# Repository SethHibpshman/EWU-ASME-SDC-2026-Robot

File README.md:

# EWU ASME SDC 2026 Robot

> A remotely controlled garbage truck robot built for the 2026 ASME Student Design Competition, featuring a custom KiCad PCB and power distribution board, Arduino iBUS teleoperation, rear wheel drive with servo steering, a robotic arm, and a rotary dumping bucket. **3rd place overall.**

> The original written papers (the full ASME SDC report and the battery analysis) are in [`/docs`](/docs). The KiCad PCB files and 3D models are in [`/hardware`](/hardware).

## Table of Contents

- [Overview](#overview)
- [Functionality](#functionality)
  - [Operating Requirements](#operating-requirements)
  - [Drive and Steering](#drive-and-steering)
  - [Manipulation and Dumping](#manipulation-and-dumping)
  - [Radio Control Mapping](#radio-control-mapping)
  - [Input Processing and Failsafe](#input-processing-and-failsafe)
- [System Design](#system-design)
  - [Hardware](#hardware)
  - [Power Architecture](#power-architecture)
  - [Battery Selection Analysis](#battery-selection-analysis)
  - [PCB Design](#pcb-design)
  - [Power Distribution Board](#power-distribution-board)
  - [Software](#software)
  - [Mechanical Design](#mechanical-design)
- [Design Tradeoffs](#design-tradeoffs)
- [Competition Results](#competition-results)
- [Lessons Learned and Future Improvements](#lessons-learned-and-future-improvements)
- [Bill of Materials](#bill-of-materials)
- [Team](#team)
- [AI Disclosure](#ai-disclosure)
- [License](#license)

## Overview

The 2026 ASME SDC challenges teams to design, fabricate, and test a versatile waste collection device that can navigate a model "downtown Dallas", collect and sort garbage and recycling, and dump it into the correct facility (landfill or recycling center) without damaging the playfield or spilling waste.

This robot is a compact, fully teleoperated garbage truck built by the Eastern Washington University ASME chapter. It combines a custom electrical system, Arduino based control logic, a FlySky radio link, a 3D printed PETG chassis, and a servo driven arm that feeds a rotary dumping bucket. It reached the final head-to-head matchup against the top-seeded team and finished **third overall**.

The electrical and control work also served as applied coursework for **EENG 163: Introduction to Embedded Systems** at Eastern Washington University.

## Functionality

### Operating Requirements

The robot had to satisfy the following competition rules:

| Category | Requirement |
|---|---|
| **Size** | Fit inside a 50 cm x 50 cm x 50 cm box, including batteries and tools |
| **Power** | Rechargeable dry cell batteries only, with onboard distribution and no tethering |
| **Control** | Single operator, single radio transmitter |
| **Runs** | 5 to 10 minute timed runs, timer never paused |
| **Repairs** | Battery swaps and wire reconnection allowed on the clock, no soldering or reprogramming |
| **Safety** | No playfield damage, no interference with other robots, unsafe behavior means disqualification |
| **Course** | Navigate 10 to 18 cm wide streets with 90 and 180 degree turns |

### Drive and Steering

| Feature | Behavior |
|---|---|
| **Rear drive** | Two geared yellow DC motors with rubber wheels, driven by a brushed DC H-bridge with forward and reverse PWM |
| **Front steering** | Servo steering through 3D printed control arms, clamped to a safe pulse range |
| **Deadband** | Neutral zone around center throttle prevents unintended motion and drift |
| **Throttle smoothing** | Exponential smoothing reduces jitter and drivetrain current spikes |

### Manipulation and Dumping

| Feature | Behavior |
|---|---|
| **Arm** | Servo driven arm with gripper and shoulder joint, designed by David Alvarado |
| **Shoulder motion** | Stepped slowly toward its target angle for smooth, controlled movement |
| **Arm to dumper slide** | At a 35 degree arm angle, nearly any material slides from the small receptacle into the dumper |
| **Rotary dumper** | Servo tips the bucket with analog control so contents slide out smoothly into the large receptacle |

### Radio Control Mapping

| Channel | Function | Pin |
|---|---|---|
| CH1 | Steering servo | D2 |
| CH2 | Drive motor throttle (FWD / REV) | D9 / D10 |
| CH3 | Auxiliary servo | D4 |
| CH5 | Gripper servo | D3 |
| CH6 | Shoulder servo | D5 |

> Mapping is taken from the firmware v10.0.0 listing. Confirm against your sketch before publishing.

### Input Processing and Failsafe

- **iBUS decoding:** frames from the FlySky FS-iA6B are read on hardware serial and parsed in software
- **Checksum validation:** corrupted frames are discarded
- **Normalization:** channel values map to roughly 1000 to 2000 µs pulse widths, then to actuator specific ranges
- **Failsafe:** the receiver returns outputs to neutral on signal loss, which stops the motors

## System Design

### Hardware

| Component | Details |
|---|---|
| Microcontroller | Arduino Nano Every |
| Radio | FlySky FS-iA6B receiver (iBUS serial) with FlySky transmitter |
| Battery | 6x NiMH AA in series, 7.2 V nominal |
| Regulation | LM2596 buck converter module, 5 V logic rail |
| Motor driver | Brushed DC H-bridge |
| Drive motors | 2x geared yellow DC motors |
| Servos | SG90 and MG995 types (see BOM) |
| Capacitance | 4x 1000 µF electrolytic (4000 µF bulk) |
| Structure | 3D printed PETG |

### Power Architecture

The design separates power into two domains so motor noise cannot reset the microcontroller.

```mermaid
flowchart LR
    BAT["6x NiMH AA pack<br/>7.2 V nominal"] --> SW["Power switch"]
    SW --> PDB["Power Distribution Board<br/>4000 uF bulk capacitance"]

    PDB -- "raw battery rail" --> HB["Brushed DC H-bridge"]
    PDB -- "raw battery rail" --> HTS["High torque servos"]
    PDB -- "soldered harness" --> BUCK["LM2596 buck converter<br/>on control PCB"]

    BUCK -- "5 V" --> MCU["Arduino Nano Every"]
    BUCK -- "5 V" --> RX["FS-iA6B receiver"]
    BUCK -- "5 V" --> LTS["Low torque servos"]

    MCU -- "PWM" --> HB
    MCU -- "servo PWM" --> HTS
    MCU -- "servo PWM" --> LTS
    HB --> MOT["2x DC drive motors"]
```

- Unregulated battery voltage feeds the motor driver and high torque servos directly, avoiding current limits and voltage drops from a regulator
- 4000 µF of bulk capacitance absorbs transients from motor acceleration and steering
- Regulation is reserved for logic level components only

### Battery Selection Analysis

Pack selection came from an EENG 163 research project (February 2026). Each pack is modeled as an ideal source with internal resistance:

$$V_{load} = V_{nominal} - I_{draw} \cdot R_{internal}$$

Targets were a **2 A** worst case load and a **6 V** minimum so the buck converter could hold a stable 5 V.

| Parameter | Alkaline 9 V | Alkaline AA | NiMH AA |
|---|---|---|---|
| Nominal voltage per cell | 9 V | 1.5 V | 1.2 V |
| Internal resistance per cell | 1.5 Ω | 0.15 Ω | 0.02 Ω |
| Max continuous current | 0.1 A | 1 A | 3 A |
| Tested pack | 1 cell | 6 in series | 6 in series |
| Pack voltage / resistance | 9 V / 1.5 Ω | 9.0 V / 0.9 Ω | 7.2 V / 0.12 Ω |
| Voltage at 2 A | 6 V | 7.2 V | 6.96 V |
| Verdict | Unsafe, 20x over rating | Over 1 A rating | Safe, most robust |

$$\text{NiMH AA (6S): } V_{load} = 7.2 - 2(0.12) = 6.96\ \text{V}$$

> The analysis assumed a brushless motor. The final robot used low draw yellow DC motors instead, so the NiMH pack ran with extra margin.

### PCB Design

Designed in KiCad and fabricated through JLCPCB. All project files are in [`/hardware/KiCAD PCB`](</hardware/KiCAD PCB>).

- LM2596 buck converter footprint for the 5 V rail
- Arduino Nano Every mounted directly on the board
- Five male pin header interfaces plus separated ground and power rails in a 5x3 layout, usable with Dupont connectors or direct soldering
- Continuous ground plane to reduce noise coupling between motor circuits and logic

### Power Distribution Board

- Four 1000 µF capacitors across the main rail
- Integrated brushed DC H-bridge for the drive motors
- Physical power switch for fast shutdown during setup and repairs
- Three 3 pin headers supplying raw battery voltage to high torque servos, with control signals routed separately from the control PCB
- Joined to the control PCB by two soldered wire harnesses for vibration resistance

### Software

Arduino sketch (version 10.0.0) running on the Nano Every, adapted from SwapnilNimbalkar's iBUS to PWM receiver tutorial. The full listing is also in the appendix of the report in [`/docs`](/docs).

**Dependencies:** `Servo`

```
firmware/    # Arduino iBUS teleoperation sketch (.ino)
```

### Mechanical Design

*Written by Zachary Jump, with arm and dumper integration by David Alvarado. CAD files are in [`/hardware/3D Models`](</hardware/3D Models>).*

#### Chassis

The chassis went through several overhauls. It began as an RC car style layout with systems mounted separately, then flipped to building the chassis around the components once subsystem designs matured. PLA was dropped for **PETG** because PLA snapped before flexing, while PETG deforms instead of fracturing.

<table>
  <tr>
    <td align="center" width="50%">
      <br>
      <em>Initial lower chassis</em>
    </td>
    <td align="center" width="50%">
      <br>
      <em>Initial full assembly</em>
    </td>
  </tr>
  <tr>
    <td align="center" width="50%">
      <br>
      <em>Chassis overhaul V3</em>
    </td>
    <td align="center" width="50%">
      <br>
      <em>Final chassis gallery</em>
    </td>
  </tr>
</table>

#### Drivetrain and Steering

Four Mecanum wheels were the first idea, but programming effort and the need for flat smooth terrain ruled them out. The final layout is rear wheel drive with servo steered front wheels.

| Steering Property | Value |
|---|---|
| Geometric maximum angle | 53 degrees (control arms go parallel and steering locks) |
| Achieved maximum angle | 32 degrees (limited by clearance around thick printed parts) |
| Servo advantage | Greatest at 0 degrees, approaches zero near 53 degrees |

<table>
  <tr>
    <td align="center" width="50%">
      <br>
      <em>Steering, front view</em>
    </td>
    <td align="center" width="50%">
      <br>
      <em>Steering, top down</em>
    </td>
  </tr>
  <tr>
    <td align="center" width="50%">
      <br>
      <em>Abandoned brushless drivetrain</em>
    </td>
    <td align="center" width="50%">
      <br>
      <em>Final yellow DC motors</em>
    </td>
  </tr>
</table>

The first rear drive used a brushless motor with a planetary gearbox, driveshaft, and bevel gears, but it drew far too much current from the pack. The two yellow DC motors draw little power, deliver the needed torque, and came with their own wheels.

#### Rotary Dumping Mechanism

The dumper sits high on the robot, which frees room underneath for electronics and drivetrain parts. A slide between the arm and the bucket guides material from the small receptacle into the dumper, and a rear mounted servo tips the bucket on a plastic pivot to dump into the large receptacle.

<table>
  <tr>
    <td align="center" width="50%">
      <br>
      <em>Dumper, top view</em>
    </td>
    <td align="center" width="50%">
      <br>
      <em>Arm slide and gear detail</em>
    </td>
  </tr>
  <tr>
    <td align="center" width="50%">
      <br>
      <em>Pivot and servo mount</em>
    </td>
    <td align="center" width="50%">
      <br>
      <em>Bucket on its own</em>
    </td>
  </tr>
</table>

## Design Tradeoffs

| Decision | Reasoning |
|---|---|
| **NiMH over LiPo** | LiPo has higher energy density but raises classification and handling concerns. NiMH is robust, widely available, meets the dry cell rule, and the AA form factor simplifies swaps |
| **Arduino over a faster MCU** | Teleoperation needs no heavy computation. Arduino kept development and debugging fast |
| **Custom PCB** | Fewer loose connections, better vibration resistance, faster troubleshooting |
| **Battery voltage to high current loads** | Avoids regulator current limits and voltage drops. Regulation reserved for logic |
| **Servo steering over Mecanum** | Simple and fast to build, at the cost of a marginal turning radius |
| **PETG over PLA** | Slightly less stiff, but bends instead of breaking |

## Competition Results

The robot completed one Initial Testing Demonstration and three Head-to-Head Elimination rounds, advanced through the bracket, and met the top-seeded team in the final matchup, finishing **third overall**.

| Observation | Outcome |
|---|---|
| NiMH pack and bulk capacitance | Reliable power with no resets, best when fully charged before each run |
| Dupont connector failures in round one | Critical connections were soldered afterward |
| Sawdust-like debris on the field | Reduced wheel traction under acceleration and turning |
| Marginal turning radius | Lots of pivoting at 90 and 180 degree corners |
| Right side arm placement | Limited approach angles to some bins |

Overall, the limits were mechanical (traction, steering geometry, subsystem placement), not electrical.

## Lessons Learned and Future Improvements

**Lessons**

- Build the chassis around the components instead of fitting components into a chassis
- Separate actuator power from logic power early
- Solder or lock every critical connection from the start
- Match the motor to the pack's internal resistance

**Future improvements**

- Larger steering angle, or a differential drive layout for tighter pivoting
- More aggressive or softer tread, and a debris clearing feature
- Arm mounted closer to the centerline
- Inline fuse and reverse polarity protection at the battery input, and servo supply voltage checked against datasheet limits at full charge
- Firmware frame timeout so motors stop even if the receiver holds its last values, plus verified receiver failsafe
- Full power budget with measured voltage under load, and a BOM kept current as parts are added

## Bill of Materials

| Item | Qty | Unit | Total |
|---|---|---|---|
| Arduino Nano Every | 1 | $18.00 | $18.00 |
| FS-iA6B/X TX/RX | 1 | $45.00 | $45.00 |
| Geared DC Motor | 2 | $1.00 | $2.00 |
| AA Battery Cage | 1 | $8.00 | $8.00 |
| Servo (SG90) | 1 | $2.00 | $2.00 |
| Servo (MG995) | 2 | $4.50 | $9.00 |
| PCB | 1 | - | $5.00 |
| PDB | 1 | - | $2.00 |
| Misc. Wires | - | - | $2.00 |
| 3D Printed Parts | - | - | $4.00 |
| **Grand Total** | | | **$97.00** |

> - Costs are taken from the written report's BOM.
> - The NiMH cells, LM2596 module, capacitors, and H-bridge are not itemized in the original table.

## Team

The robot was designed and built by three subsystem leads, who carried it through to competition.

**Seth A. Hibpshman**  
Student of Electrical and Computer Engineering, Eastern Washington University  
Electrical system, custom PCB, power distribution board, battery analysis, firmware

**Zachary Jump**  
Student of Mechanical Engineering, Eastern Washington University  
Chassis, drivetrain, steering, rotary dumping mechanism

**David Alvarado**  
Student of Mechanical Engineering, Eastern Washington University  
Robotic arm

American Society of Mechanical Engineers, Eastern Washington University Chapter.

**Additional Contributors**

Thank you to the other members of the EWU ASME chapter who had contributions earlier in the season. Their work on research and brainstorming helped shape the project, and the final design builds on it. *If you did not receive recognition for your work on this project, please reach out to shibpshman1@ewu.edu to be named in this additional contributors section.*

## AI Disclosure
_AI (LLM) tools were used in the drafting and editing of this README; the project design, hardware, and firmware are the team's own work._

## License

[LICENSE](LICENSE)

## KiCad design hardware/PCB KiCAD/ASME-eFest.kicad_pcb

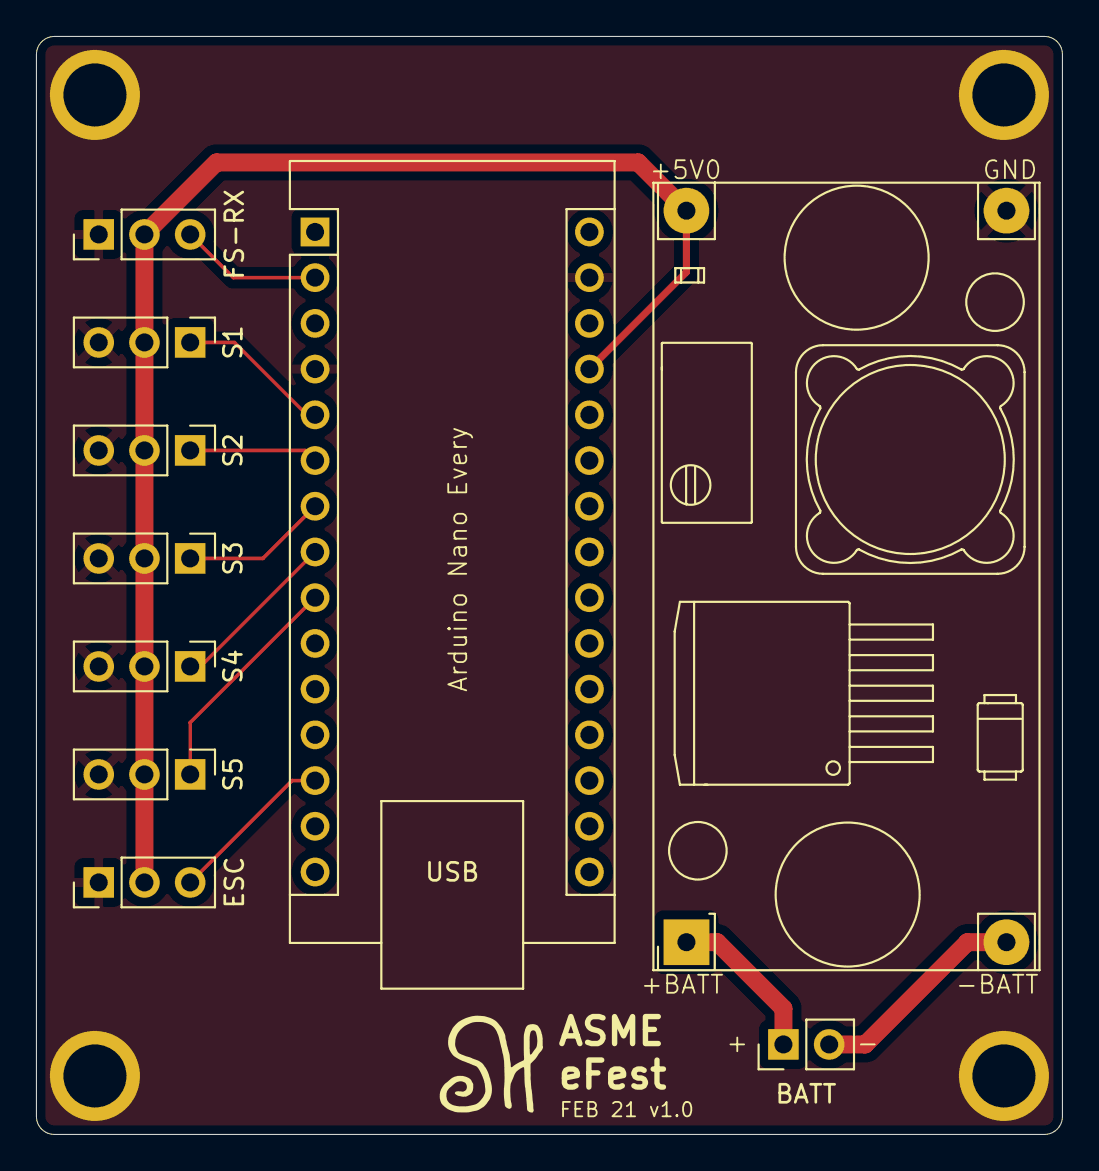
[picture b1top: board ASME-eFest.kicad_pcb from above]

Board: 2 copper layers, 57.0 x 61.0 mm, 10 parts (0 on the bottom side), 11 nets.

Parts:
A2: Arduino_Nano_Every; Arduino_Nano
BATT: PinHeader_1x02_P2.54mm_Vertical
ESC: ESC; PinHeader_1x03_P2.54mm_Vertical
FS-RX: PinHeader_1x03_P2.54mm_Vertical
S1, S2, S3, S4, S5: Motor_Servo; PinHeader_1x03_P2.54mm_Vertical
U1: DCDC_StepDown; YAAJ_DCDC_StepDown_LM2596

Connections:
+5V: A2.27 (+5V), ESC.2 (S_VCC), FS-RX.1 (VCC), S1.2 (+), S2.2 (+), S3.2 (+), S4.2 (+), S5.2 (+), U1.4 (Vout)
+BATT: BATT.1, U1.1 (Vin)
-BATT: BATT.2, U1.2 (GND)
GND: A2.4 (GND), A2.29 (GND), ESC.1 (S_GND), FS-RX.2 (GND), S1.3 (-), S2.3 (-), S3.3 (-), S4.3 (-), S5.3 (-), U1.3 (GND)
unnamed: A2.5 (D2), S1.1 (PWM)
unnamed: A2.6 (D3), S2.1 (PWM)
unnamed: A2.7 (D4), S3.1 (PWM)
unnamed: A2.8 (D5), S4.1 (PWM)
unnamed: A2.9 (D6), S5.1 (PWM)
unnamed: A2.13 (D10), ESC.3 (Signal)
unnamed: A2.2 (RX1), FS-RX.3 (IBUS_TX)
